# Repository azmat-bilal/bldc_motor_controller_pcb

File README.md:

# bldc_motor_controller_pcb
A Brushless DC Motor controller board. The design is inspired and is compatible with Odrive project (https://github.com/madcowswe/ODriveHardware) except that this one is single channel.

# Sponsorship
Huge thanks to Mouser Elecotronics (www.mouser.com) to sponsor components to build and test the design.

![Sponsor]( 
https://github.com/azmat-bilal/bldc_motor_controller_pcb/blob/master/bldc_motor_cntroller/mouser_logo.jpeg)

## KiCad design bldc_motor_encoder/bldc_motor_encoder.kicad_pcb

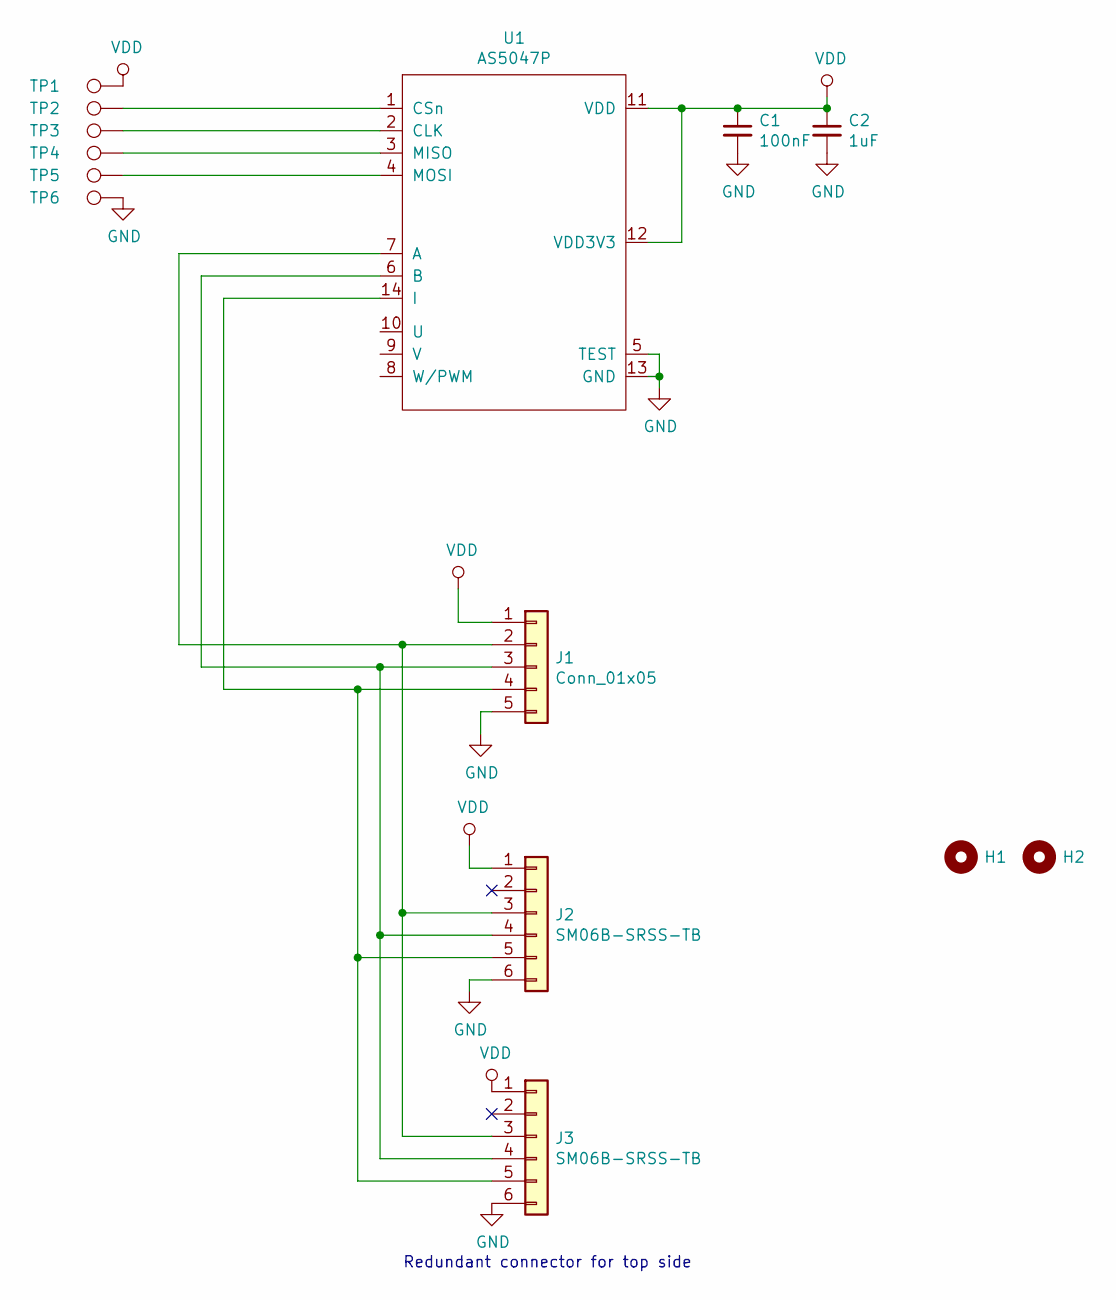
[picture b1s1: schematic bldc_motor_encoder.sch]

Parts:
C1: 100nF; C_0402_1005Metric
C2: 1uF; C_0402_1005Metric
H1, H2: MountingHole; MountingHole_3.2mm_M3_DIN965_Pad
J1: Conn_01x05; PinHeader_1x05_P2.54mm_Horizontal
J2, J3: SM06B-SRSS-TB; JST_SH_SM06B-SRSS-TB_1x06-1MP_P1.00mm_Horizontal
TP1, TP2, TP3, TP4, TP5, TP6: TestPoint; TestPoint_Pad_D1.5mm
U1: AS5047P; TSSOP-14_4.4x5mm_P0.65mm

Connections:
GND: C1.2, C2.2, J1.5, J2.6, J3.6, TP6.1, U1.5 (TEST), U1.13 (GND)
unnamed: J1.2, J2.3, J3.3, U1.7 (A)
unnamed: J1.3, J2.4, J3.4, U1.6 (B)
unnamed: J1.4, J2.5, J3.5, U1.14 (I)
unnamed: TP2.1, U1.1 (CSn)
unnamed: TP3.1, U1.2 (CLK)
unnamed: TP4.1, U1.3 (MISO)
unnamed: TP5.1, U1.4 (MOSI)
VDD: C1.1, C2.1, J1.1, J2.1, J3.1, TP1.1, U1.11 (VDD), U1.12 (VDD3V3)

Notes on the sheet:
Redundant connector for top side

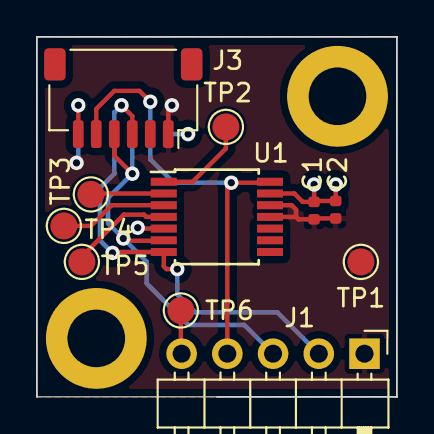
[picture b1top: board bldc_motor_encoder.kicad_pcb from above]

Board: 2 copper layers, 20.0 x 20.0 mm, 14 parts (1 on the bottom side), 9 nets.

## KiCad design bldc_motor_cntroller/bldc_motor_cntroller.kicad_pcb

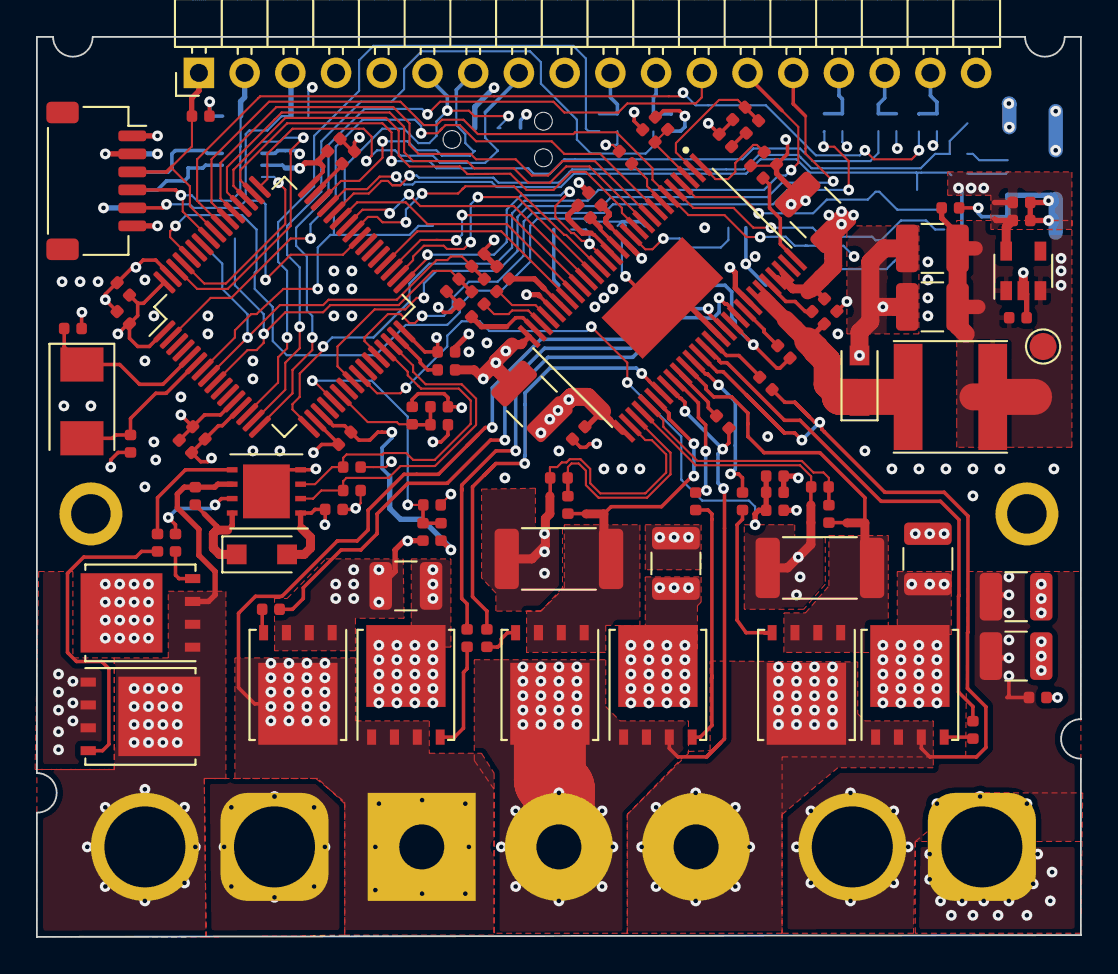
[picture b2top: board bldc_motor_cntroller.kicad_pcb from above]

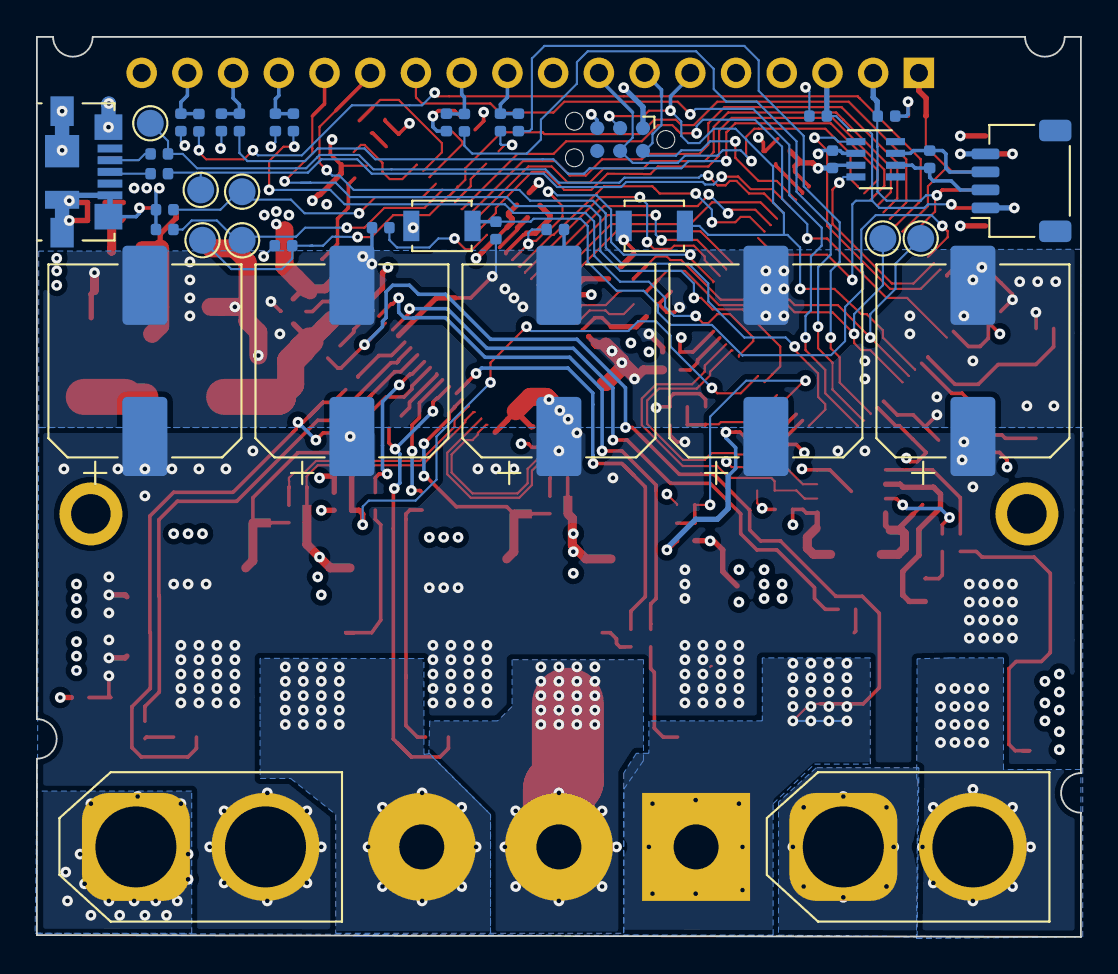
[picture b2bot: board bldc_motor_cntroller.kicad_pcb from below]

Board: 4 copper layers, 58.0 x 50.0 mm, 146 parts (46 on the bottom side), 105 nets.

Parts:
C1, C2, C3, C4, C5, C38: 82pF; C_0402_1005Metric
C6, C16, C47, C48, C49, C50, C51, C52: 100nF; C_0402_1005Metric
C7, C8, C9, C10, C58: 150uF 63V poly; CP_Elec_10x14.3
C11, C12: 10uF 63V; C_1210_3225Metric
C13, C24, C26: 0.1uF 100V; C_0402_1005Metric
C14, C39: 270pF; C_0402_1005Metric
C15, C21: 2.2uF 25V; C_0402_1005Metric
C17, C18: 1uF 10V; C_0402_1005Metric
C19: 0.1uF 25V; C_0402_1005Metric
C20, C33: 2.2uF 16V; C_0402_1005Metric
C22, C23, C36: 1uF 25V; C_0402_1005Metric
C25, C27: 4.7uF 100V; C_1210_3225Metric
C28, C29, C31, C32: 0.1uF 50V; C_0402_1005Metric
C30: 0.022uF 50V; C_0402_1005Metric
C34, C35: 47uF 16V; C_1210_3225Metric
C37, C41: 2200pF; C_0402_1005Metric
C40: 15nF; C_0402_1005Metric
C42, C43, C44: 2.2uF 100V; C_1210_3225Metric
C45, C46: 2200PF; C_0402_1005Metric
C53: 1uF; C_0402_1005Metric
C54, C55: 2.2uF; C_0402_1005Metric
C56, C57: 12pF; C_0402_1005Metric
D1: MBR140SFT1G; D_SOD-123F
D2: 100V 2A SMB; D_SOD-123F
H1, H2: MountingHole_Pad; MountingHole_2.2mm_M2_ISO7380_Pad
HS1, HS2, HS3: Heatsink; heatsink14x14x6
J1: SM06B-SRSS-TB(LF)(SN); JST_SH_SM06B-SRSS-TB_1x06-1MP_P1.00mm_Horizontal
J2: Conn_01x18; PinHeader_1x18_P2.54mm_Horizontal
J3: SM04B-SRSS-TB(LF)(SN); JST_SH_SM04B-SRSS-TB_1x04-1MP_P1.00mm_Horizontal
J5: 0473460001; USB_Micro-B_Molex_47346-0001
J6: TC2030 Tag-connect; Tag-Connect_TC2030-IDC-NL_2x03_P1.27mm_Vertical
J8, J9: XT60; AMASS_XT60-M_1x02_P7.20mm_Vertical
J10: MR30PW-M 15A (30A); SolderWirePad_1x03_P7.62mm_Drill2.5mm
L1: 33uH 1.4A; L_Taiyo-Yuden_NR-60xx
NT1, NT2, NT3, NT4: Net-Tie_2; NetTie-2_SMD_Pad0.5mm
Q1, Q2, Q3, Q4, Q5, Q6, Q7, Q8: CSD18540Q5B; TDSON-8-1
R1, R2, R6, R7, R8: 0R; R_0402_1005Metric
R3, R4, R5, R16, R17, R19, R23, R28, R31: 3.3k; R_0402_1005Metric
R9, R10: 22R; R_0402_1005Metric
R11, R13, R25, R26, R27: 10k; R_0402_1005Metric
R12, R39, R40: 120R; R_0402_1005Metric
R14, R21: 1k; R_0402_1005Metric
R15, R18, R33, R34, R35, R36, R37, R38: 2R2; R_0402_1005Metric
R20: 220k 1%; R_0402_1005Metric
R22, R24: 18k; R_0402_1005Metric
R29, R32: 22R 1%; R_0402_1005Metric
R30: 47k 1%; R_0402_1005Metric
R41, R42: 500uOhm 6W 1%; R_2512_6332Metric
SW1, SW2: B3U-1000P-B; SW_SPST_B3U-1000P
TH1, TH2: 10k; R_0402_1005Metric
TP2, TP3, TP4, TP5, TP6, TP7, TP8, TP9: TestPoint; TestPoint_Pad_D1.5mm
U1: TCAN332GDCNT; SOT-23-8
U2: TLV75733PDBV; SOT-23-5
U3: LM5109BSD; WSON-8_4x4mm_P0.8mm
U4: DRV8301DCAR; SOP50P810X120-57N
U5: STM32F405RGTx; LQFP-64_10x10mm_P0.5mm
Y1: 8MHz; Crystal_SMD_Abracon_ABM3-2Pin_5.0x3.2mm

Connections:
+5V: C17.1, C34.1, C35.1, C36.1, J1.2, J2.4, L1.2, R22.2, TP7.1, U2.1, U2.3
/I/O Interface/BOOT0: R11.2, SW1.2, U5.60
/I/O Interface/CAN_D: U1.1, U5.62
/I/O Interface/CAN_R: U1.4, U5.61
/I/O Interface/DEBUG_SWCLK: J2.8, J6.4, U5.49
/I/O Interface/DEBUG_SWDIO: J2.7, J6.2, U5.46
/I/O Interface/DEBUG_nRESET: J2.6, J6.3, SW2.2, U5.7
/I/O Interface/ENC_A: J1.3, J2.1, R5.2, U5.56
/I/O Interface/ENC_B: J1.4, J2.2, R4.2, U5.57
/I/O Interface/ENC_Z: J1.5, J2.3, R3.2, U5.40
/I/O Interface/GPIO_1: R1.2, U5.14
/I/O Interface/GPIO_2: R2.2, U5.15
/I/O Interface/GPIO_3: J2.12, U5.16
/I/O Interface/GPIO_4: J2.13, U5.17
/I/O Interface/GPIO_5: J2.14, U5.24
/I/O Interface/GPIO_6: R6.2, U5.28
/I/O Interface/GPIO_7: R7.2, U5.50
/I/O Interface/GPIO_8: R8.2, U5.55
/I/O Interface/USB_DM: R10.1, TP3.1, U5.44
/I/O Interface/USB_DP: R9.1, TP2.1, U5.45
/Microcontroller Interface/AUX_H: R17.2, U3.2, U5.30
/Microcontroller Interface/AUX_L: R16.2, U3.3, U5.29
/Microcontroller Interface/AUX_TEMP: C20.1, R19.2, TH1.2, U5.21
/Microcontroller Interface/EN_GATE: R21.2, U4.16, U5.33
/Microcontroller Interface/M0_AH: U4.17, U5.41
/Microcontroller Interface/M0_AL: U4.18, U5.34
/Microcontroller Interface/M0_BH: U4.19, U5.42
/Microcontroller Interface/M0_BL: U4.20, U5.35
/Microcontroller Interface/M0_CH: U4.21, U5.43
/Microcontroller Interface/M0_CL: U4.22, U5.36
/Microcontroller Interface/M0_TEMP: C33.1, R28.2, TH2.2, U5.25
/Microcontroller Interface/SPI_M0_nCS: U4.8, U5.2
/Microcontroller Interface/SPI_MISO: U4.10, U5.52
/Microcontroller Interface/SPI_MOSI: U4.9, U5.53
/Microcontroller Interface/SPI_SCK: U4.11, U5.51
/Microcontroller Interface/VBUS_S: C14.1, R13.2, R14.1, U5.22
/Microcontroller Interface/nFAULT: R26.1, TP5.1, U4.6, U5.54
/Motor Driver/AVDD: C22.1, U4.27
/Motor Driver/CSENSE_1: C37.2, R29.2, TP8.1, U5.8
/Motor Driver/CSENSE_2: C41.2, R32.2, TP9.1, U5.9
/Motor Driver/DVDD: C23.1, U4.23
/Motor Driver/GH_A: R33.1, U4.47
/Motor Driver/GH_B: R34.1, U4.42
/Motor Driver/GH_C: R35.1, U4.37
/Motor Driver/GL_A: R36.1, U4.45
/Motor Driver/GL_B: R37.1, U4.40
/Motor Driver/GL_C: R38.1, U4.35
/Motor Driver/PWRGD: R25.1, TP4.1, U4.4
/Motor Driver/SH_A: C28.1, J10.1, Q3.1, Q3.2, Q3.3, Q6.5, U4.46
/Motor Driver/SH_B: C29.1, J10.3, Q4.1, Q4.2, Q4.3, Q7.5, U4.41
/Motor Driver/SH_C: C32.1, J10.2, Q5.1, Q5.2, Q5.3, Q8.5, U4.36
/Motor Driver/SL_B: NT2.2, Q7.1, Q7.2, Q7.3, R42.2, U4.39
/Motor Driver/SL_C: NT1.2, Q8.1, Q8.2, Q8.3, R41.2, U4.34
/Motor Driver/SN1: C46.2, R40.1, U4.33
/Motor Driver/SN2: C45.2, R39.1, U4.31
/Motor Driver/SP1: C46.1, NT4.1, U4.32
/Motor Driver/SP2: C45.1, NT3.1, U4.30
/Motor Driver/nOCTW: R27.1, TP6.1, U4.5
GND: C1.2, C2.2, C3.2, C4.2, C5.2, C6.1, C7.2, C8.2, C9.2, C10.2, C11.2, C12.2, C13.2, C14.2, C15.2, C17.2, C18.2, C19.2, C20.2, C21.2, C22.2, C23.2, C24.2, C25.2, C26.2, C27.2, C33.2, C34.2, C35.2, C36.2, C37.1, C38.2, C39.2, C40.1, C41.1, C42.2, C43.2, C44.2, C47.2, C48.2, C49.2, C50.2, C51.2, C52.2, C53.2, C54.2, C55.2, C56.1, C57.1, C58.2, D2.2, J1.6, J2.5, J2.18, J3.4, J5.5, J5.6, J6.5, J8.1, J9.1, NT3.2, NT4.2, Q2.1, Q2.2, Q2.3, Q6.1, Q6.2, Q6.3, R11.1, R14.2, R16.1, R17.1, R19.1, R20.2, R21.1, R23.1, R24.2, R28.1, R31.1, R41.1, R42.1, SW2.1, U1.2, U2.2, U3.4, U3.9, U4.28, U4.44, U4.57, U5.12, U5.18, U5.63
GVDD: C15.1, C21.1, D1.2, U3.1, U4.13
unnamed: C1.1, J2.10, R1.1
unnamed: C2.1, J2.11, R2.1
unnamed: C3.1, J2.15, R6.1
unnamed: C4.1, J2.16, R7.1
unnamed: C5.1, J2.17, R8.1
unnamed: C16.1, D1.1, U3.8
unnamed: C16.2, J9.2, Q1.1, Q1.2, Q1.3, Q2.5, U3.6
unnamed: C28.2, U4.48
unnamed: C29.2, U4.43
unnamed: C30.1, U4.14
unnamed: C30.2, U4.15
unnamed: C31.1, D2.1, L1.1, U4.50, U4.51
unnamed: C31.2, U4.52
unnamed: C32.2, U4.38
unnamed: C38.1, R30.1, U4.2
unnamed: C39.1, R30.2
unnamed: C40.2, U4.56
unnamed: C54.1, U5.31
unnamed: C55.1, U5.47
unnamed: C56.2, U5.5, Y1.1
unnamed: C57.2, U5.6, Y1.2
unnamed: J3.2, R12.1, U1.6
unnamed: J3.3, R12.2, U1.7
unnamed: J5.2, R10.2
unnamed: J5.3, R9.2
unnamed: NT1.1, R39.2
unnamed: NT2.1, R40.2
unnamed: Q1.4, R15.2
unnamed: Q2.4, R18.2
unnamed: Q3.4, R33.2
unnamed: Q4.4, R34.2
unnamed: Q5.4, R35.2
unnamed: Q6.4, R36.2
unnamed: Q7.4, R37.2
unnamed: Q8.4, R38.2
unnamed: R15.1, U3.7
unnamed: R18.1, U3.5
unnamed: R20.1, U4.1
unnamed: R22.1, R23.2, U4.3
unnamed: R24.1, U4.7
unnamed: R29.1, U4.25
unnamed: R31.2, U4.12
unnamed: R32.1, U4.26
VDC: C7.1, C8.1, C9.1, C10.1, C11.1, C12.1, C13.1, C24.1, C25.1, C26.1, C27.1, C42.1, C43.1, C44.1, C58.1, J8.2, Q1.5, Q3.5, Q4.5, Q5.5, R13.1, U4.29, U4.53, U4.54
VDD: C6.2, C18.1, C19.1, C47.1, C48.1, C49.1, C50.1, C51.1, C52.1, C53.1, J1.1, J2.9, J3.1, J6.1, R3.1, R4.1, R5.1, R25.2, R26.2, R27.2, SW1.1, TH1.1, TH2.1, U1.3, U2.5, U4.24, U4.49, U5.1, U5.13, U5.19, U5.32, U5.48, U5.64

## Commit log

2020-01-26 first commit. created the kicad project.
2020-01-26 adding sub sheets. completed the mcu interface.
2020-01-26 adding drv8301 lib in the project.
2020-01-26 interfacing the drv8301 pre-driver.
2020-01-27 finished motor driver interface.
2020-01-27 added braking circuit. added encoder interface.
2020-01-28 fixed typo in readme
2020-01-29 schematic annotation. added bulk caps. moved shunt res to powersheet.
2020-01-29 added page titles and rev. no.
2020-01-29 removed redundant files.
2020-01-29 added .sch-bak to ignore list.
2020-01-29 removed .sch-bak files
2020-01-29 generated schematics pdf
2020-01-30 added missing footprints.
2020-02-05 combined 2.54p connectors. changed diode footprint.
2020-02-05 finished placement of major components.
2020-02-05 adding footprint lib table file.
2020-02-06 fixed a typo
2020-02-06 swapped connections for better routing. highlighted serial gpios.
2020-02-06 changed the motor conn. for thicker wires.
2020-02-06 finished placement. reduced pcb size.
2020-02-08 increase layer count to 4. routinng cont. swapped motor outputs.
2020-02-10 pcb routing cont. swapped 2 motor output pins for better routing.
2020-02-15 added heatsink model in the design
2020-02-15 changed the SMD connector to JST SH (from JST SHL)
2020-02-15 finished routing. DRC check pass with some known voilations.
2020-02-15 generated pdf for pcb layers and rendered images
2020-02-15 added images to the readme
2020-02-16 improved assembly documentation
2020-02-16 updated pdf documentation
2020-02-16 generated gerber and drill files
2020-02-16 adding the BOM and fab zip file.
2020-02-17 created a sub project for AS5047 encoder pcb. finish sch and pcb
2020-02-17 modified library name. added AS5047 Part.
2020-02-17 generated output files for the encode pcb
2020-02-17 committing .bck .dcm and cache.lib files.
2020-03-01 improved BOM
2020-03-01 adding sponsor logo
2020-03-01 updated readme to add sponsor info
2020-06-23 adding component BOM ( 2x controller pcb, 2x encoder pcb)
